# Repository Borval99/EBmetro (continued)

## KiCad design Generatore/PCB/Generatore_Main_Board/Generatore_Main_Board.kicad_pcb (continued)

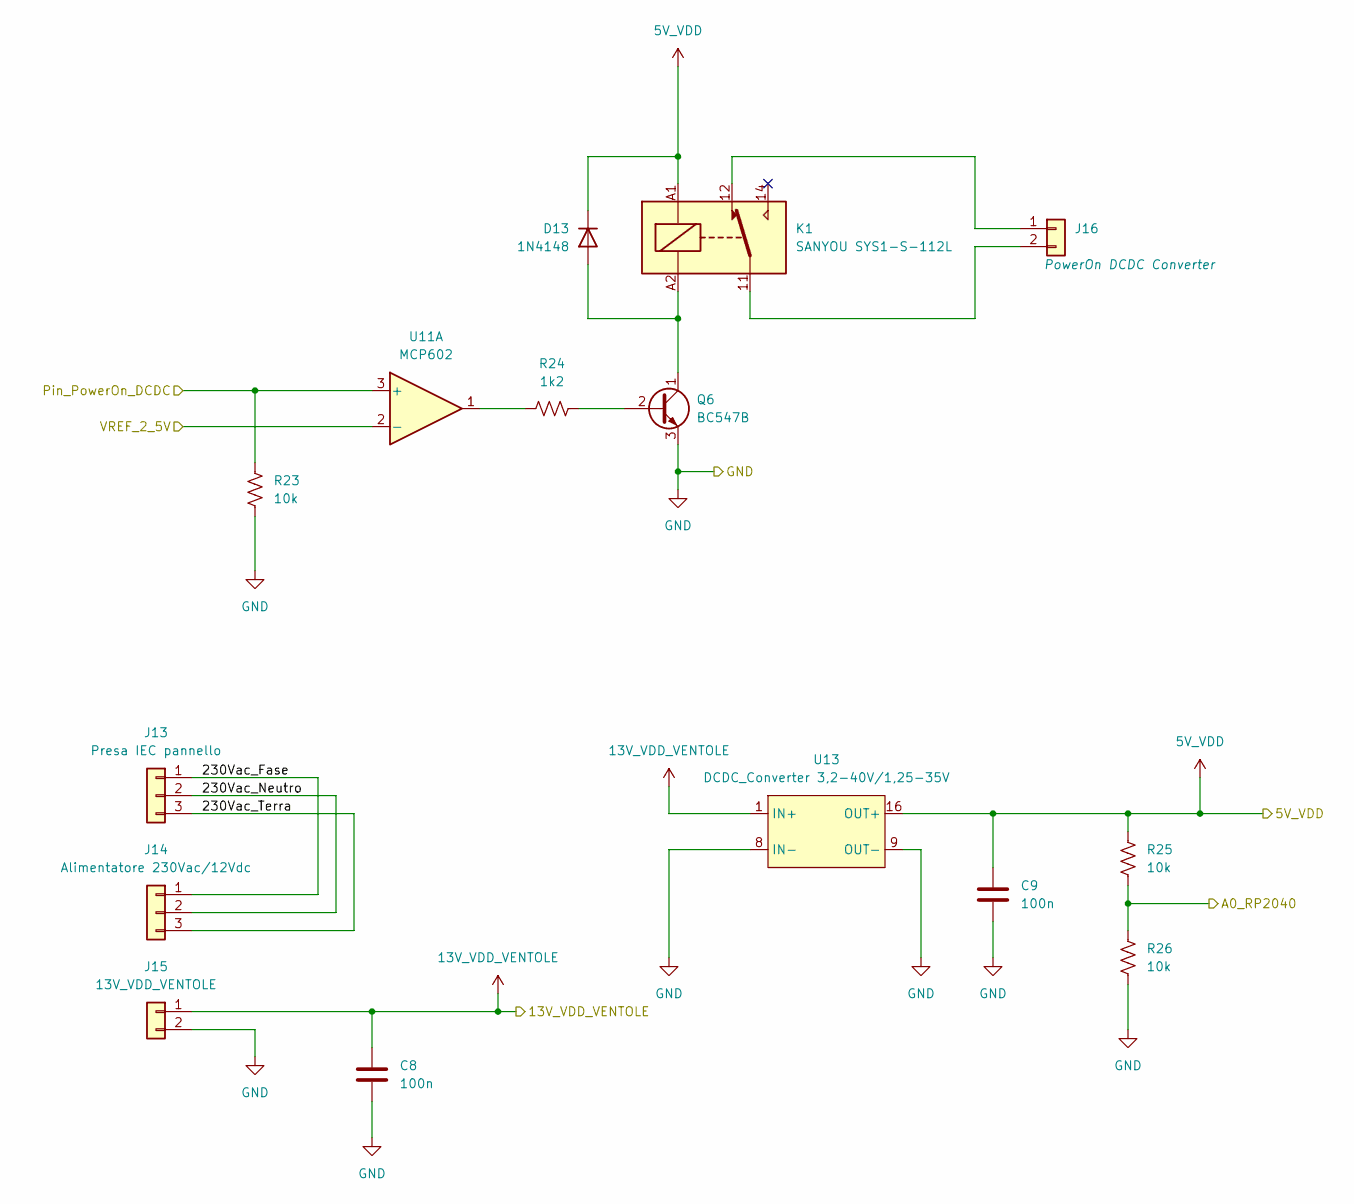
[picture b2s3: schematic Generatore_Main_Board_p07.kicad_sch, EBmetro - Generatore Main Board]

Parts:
C8, C9: 100n; Term_Block_1x2_P5mm
D13: 1N4148; D_DO-35_SOD27_P7.62mm_Horizontal
J13: Presa IEC pannello; TerminalBlock_Phoenix_MKDS-3-3-5.08_1x03_P5.08mm_Horizontal
J14: Alimentatore 230Vac/12Vdc; TerminalBlock_Phoenix_MKDS-3-3-5.08_1x03_P5.08mm_Horizontal
J15: 13V_VDD_VENTOLE; TerminalBlock_Phoenix_MKDS-3-2-5.08_1x02_P5.08mm_Horizontal
J16: Conn_01x02; JST_EH_B2B-EH-A_1x02_P2.50mm_Vertical
K1: SANYOU SYS1-S-112L; Relay_SPDT_Sanyou_SYS1-S-112L
Q6: BC547B; TO-92_Inline
R23, R25, R26: 10k; R_Axial_DIN0207_L6.3mm_D2.5mm_P10.16mm_Horizontal
R24: 1k2; R_Axial_DIN0207_L6.3mm_D2.5mm_P10.16mm_Horizontal
U11: MCP602; CERDIP-8_W7.62mm_SideBrazed_LongPads_Socket
U13: DCDC_Converter 3,2-40V/1,25-35V; DCDC_Converter 3,2-40V_1,25-35V

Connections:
5V_VDD: C9.1, D13.1 (K), K1.A1, R25.1, U13.16 (OUT+); also elsewhere on the board
13V_VDD_VENTOLE: C8.1, J15.1, U13.1 (IN+); also elsewhere on the board
/ADCs and Signal Conversion/VREF_2_5V: U11.2 (-); also elsewhere on the board
/CPUs/A0_RP2040: R25.2, R26.1; also elsewhere on the board
/CPUs/Pin_PowerOn_DCDC: R23.1, U11.3 (+); also elsewhere on the board
/Power and related/230Vac_Fase: J13.1, J14.1
/Power and related/230Vac_Neutro: J13.2, J14.2
/Power and related/230Vac_Terra: J13.3, J14.3
GND: C8.2, C9.2, J15.2, Q6.3 (E), R23.2, R26.2, U13.8 (IN-), U13.9 (OUT-); also elsewhere on the board
unnamed: D13.2 (A), K1.A2, Q6.1 (C)
unnamed: J16.1, K1.12
unnamed: J16.2, K1.11
unnamed: Q6.2 (B), R24.2
unnamed: R24.1, U11.1

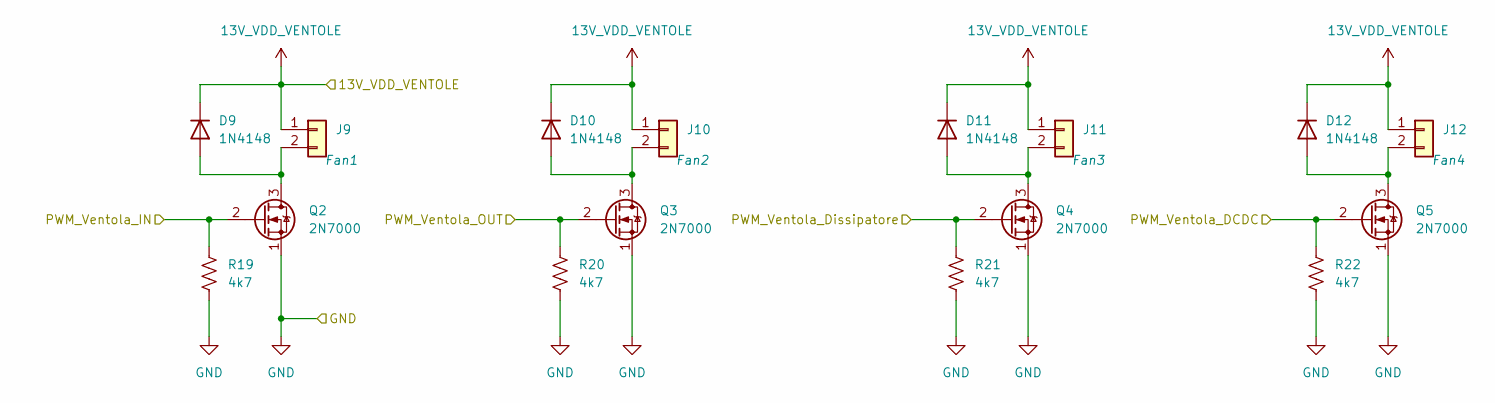
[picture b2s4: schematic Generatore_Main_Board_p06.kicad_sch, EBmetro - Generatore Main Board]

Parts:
D9, D10, D11, D12: 1N4148; D_DO-35_SOD27_P7.62mm_Horizontal
J9, J10, J11, J12: Conn_01x02; JST_XH_B2B-XH-A_1x02_P2.50mm_Vertical
Q2, Q3, Q4, Q5: 2N7000; TO-92_Inline
R19, R20, R21, R22: 4k7; R_Axial_DIN0207_L6.3mm_D2.5mm_P10.16mm_Horizontal

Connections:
13V_VDD_VENTOLE: D9.1 (K), D10.1 (K), D11.1 (K), D12.1 (K), J9.1, J10.1, J11.1, J12.1; also elsewhere on the board
/CPUs/PWM_Ventola_DCDC: Q5.2 (G), R22.1; also elsewhere on the board
/CPUs/PWM_Ventola_Dissipatore: Q4.2 (G), R21.1; also elsewhere on the board
/CPUs/PWM_Ventola_IN: Q2.2 (G), R19.1; also elsewhere on the board
/CPUs/PWM_Ventola_OUT: Q3.2 (G), R20.1; also elsewhere on the board
GND: Q2.1 (S), Q3.1 (S), Q4.1 (S), Q5.1 (S), R19.2, R20.2, R21.2, R22.2; also elsewhere on the board
unnamed: D9.2 (A), J9.2, Q2.3 (D)
unnamed: D10.2 (A), J10.2, Q3.3 (D)
unnamed: D11.2 (A), J11.2, Q4.3 (D)
unnamed: D12.2 (A), J12.2, Q5.3 (D)

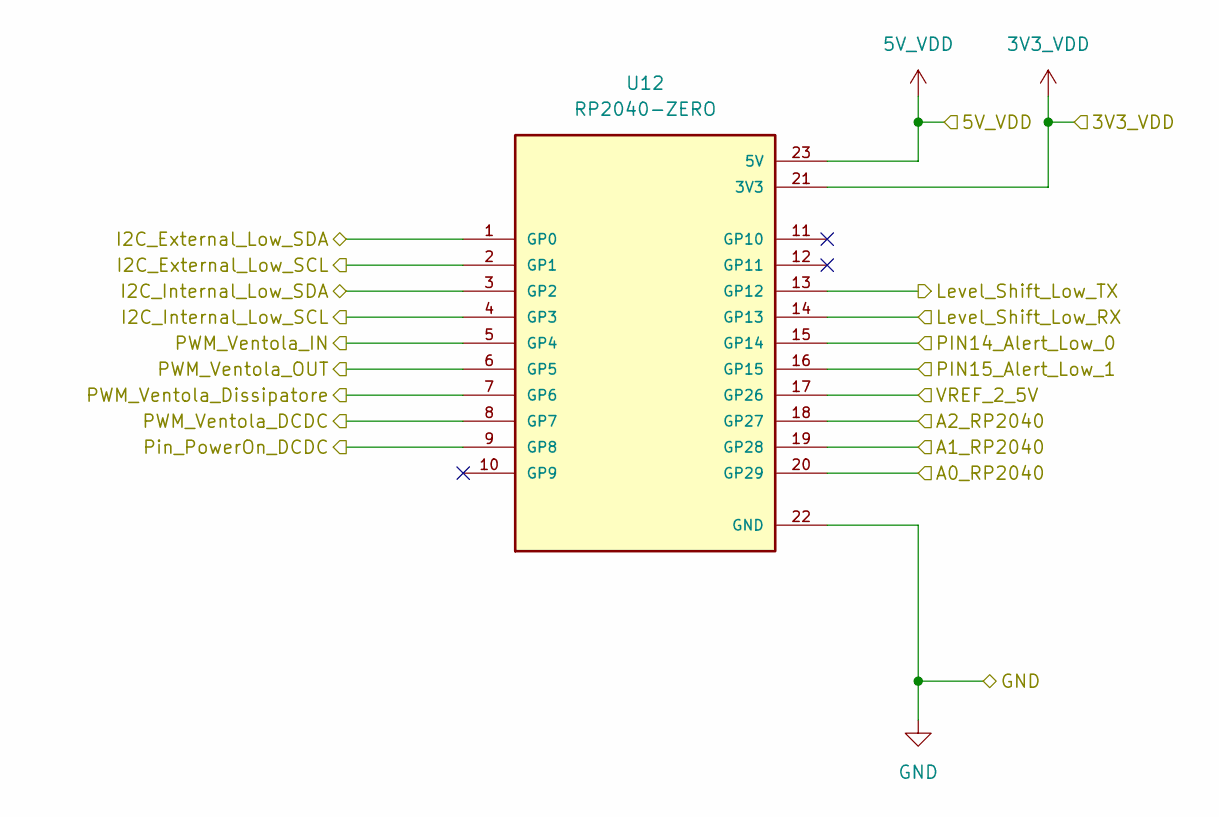
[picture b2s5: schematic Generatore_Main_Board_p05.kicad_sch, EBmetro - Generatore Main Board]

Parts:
U12: RP2040-ZERO; MODULE_RP2040-ZERO; PARTREV NA

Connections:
3V3_VDD: U12.21 (3V3); also elsewhere on the board
5V_VDD: U12.23 (5V); also elsewhere on the board
/ADCs and Signal Conversion/I2C_External_Low_SCL: U12.2 (GP1); also elsewhere on the board
/ADCs and Signal Conversion/I2C_External_Low_SDA: U12.1 (GP0); also elsewhere on the board
/ADCs and Signal Conversion/I2C_Internal_Low_SCL: U12.4 (GP3); also elsewhere on the board
/ADCs and Signal Conversion/I2C_Internal_Low_SDA: U12.3 (GP2); also elsewhere on the board
/ADCs and Signal Conversion/Level_Shift_Low_RX: U12.14 (GP13); also elsewhere on the board
/ADCs and Signal Conversion/Level_Shift_Low_TX: U12.13 (GP12); also elsewhere on the board
/ADCs and Signal Conversion/PIN14_Alert_Low_0: U12.15 (GP14); also elsewhere on the board
/ADCs and Signal Conversion/PIN15_Alert_Low_1: U12.16 (GP15); also elsewhere on the board
/ADCs and Signal Conversion/VREF_2_5V: U12.17 (GP26); also elsewhere on the board
/CPUs/A0_RP2040: U12.20 (GP29); also elsewhere on the board
/CPUs/A1_RP2040: U12.19 (GP28); also elsewhere on the board
/CPUs/A2_RP2040: U12.18 (GP27); also elsewhere on the board
/CPUs/PWM_Ventola_DCDC: U12.8 (GP7); also elsewhere on the board
/CPUs/PWM_Ventola_Dissipatore: U12.7 (GP6); also elsewhere on the board
/CPUs/PWM_Ventola_IN: U12.5 (GP4); also elsewhere on the board
/CPUs/PWM_Ventola_OUT: U12.6 (GP5); also elsewhere on the board
/CPUs/Pin_PowerOn_DCDC: U12.9 (GP8); also elsewhere on the board
GND: U12.22 (GND); also elsewhere on the board

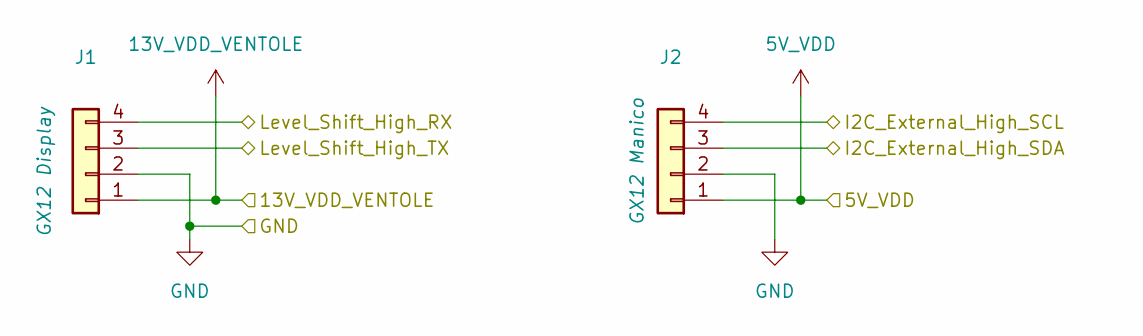
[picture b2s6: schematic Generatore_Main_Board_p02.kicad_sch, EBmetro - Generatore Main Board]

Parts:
J1, J2: Conn_01x04; JST_XH_B4B-XH-A_1x04_P2.50mm_Vertical

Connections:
5V_VDD: J2.1; also elsewhere on the board
13V_VDD_VENTOLE: J1.1; also elsewhere on the board
/ADCs and Signal Conversion/I2C_External_High_SCL: J2.4; also elsewhere on the board
/ADCs and Signal Conversion/I2C_External_High_SDA: J2.3; also elsewhere on the board
/ADCs and Signal Conversion/Level_Shift_High_RX: J1.4; also elsewhere on the board
/ADCs and Signal Conversion/Level_Shift_High_TX: J1.3; also elsewhere on the board
GND: J1.2, J2.2; also elsewhere on the board

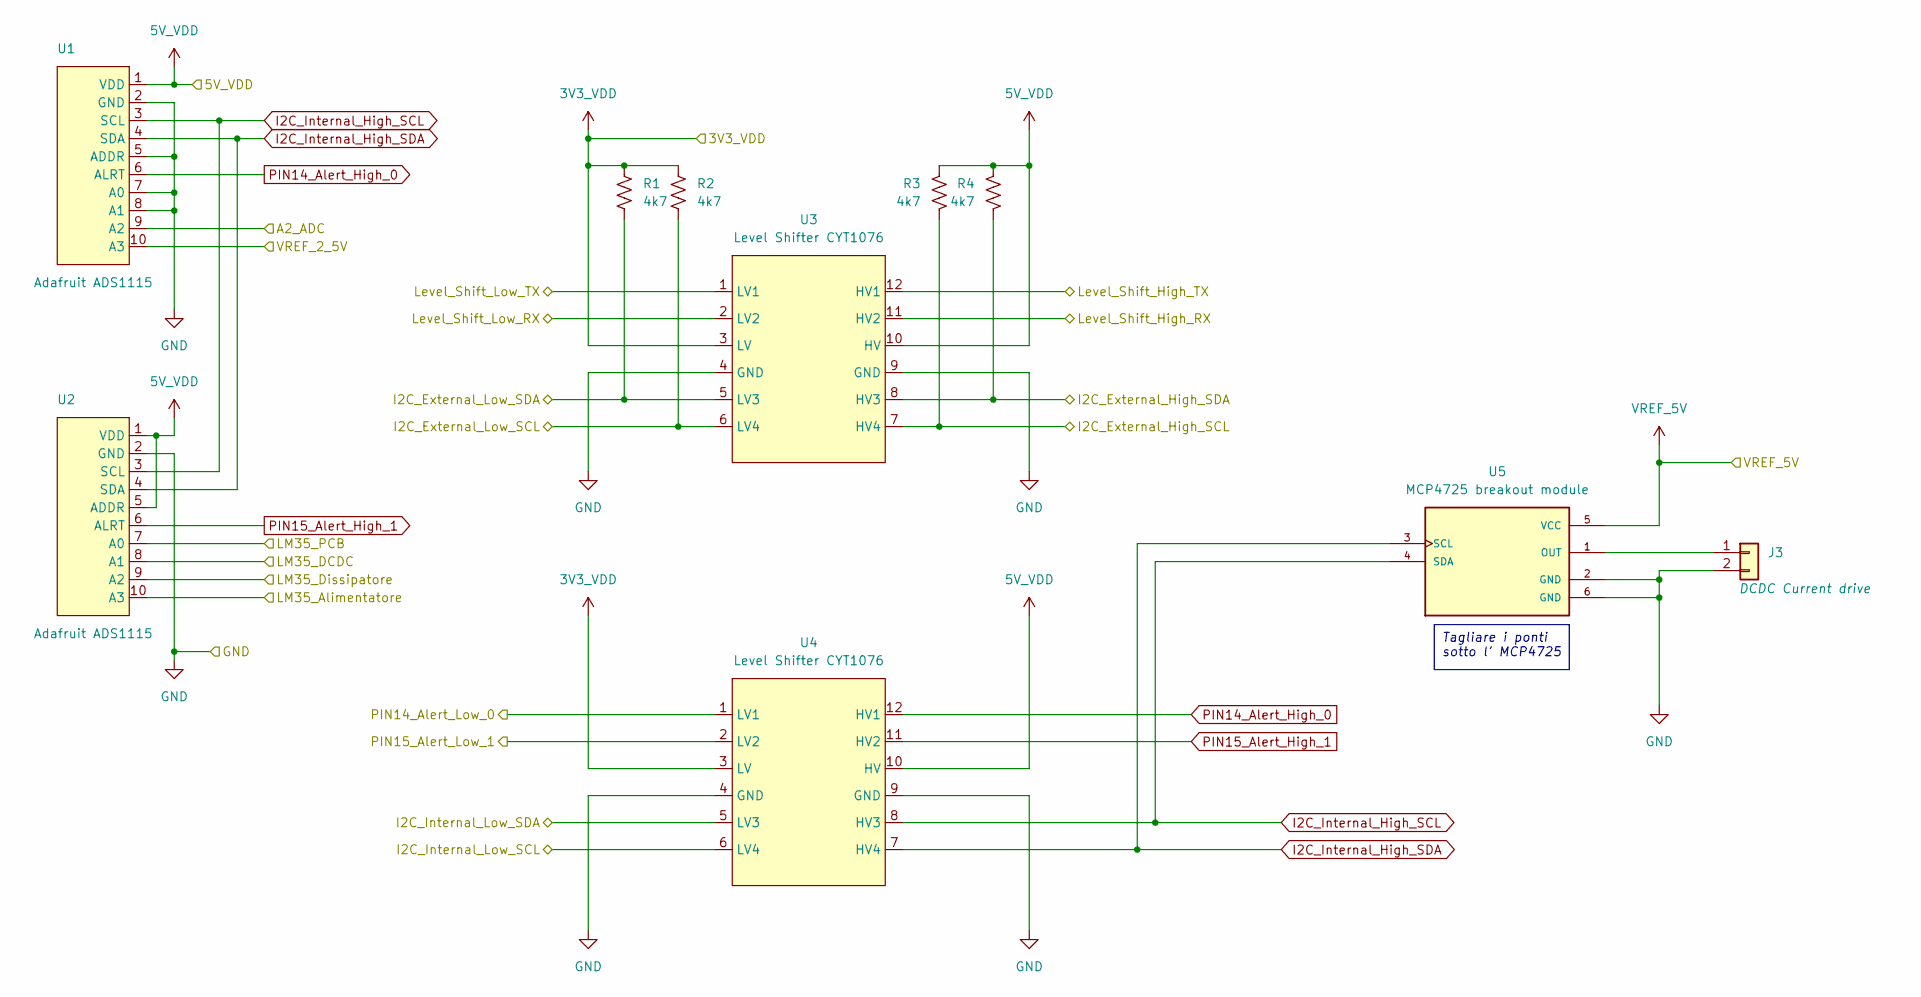
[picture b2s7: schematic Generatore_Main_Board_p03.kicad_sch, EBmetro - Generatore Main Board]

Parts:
J3: Conn_01x02; JST_EH_B2B-EH-A_1x02_P2.50mm_Vertical
R1, R2, R3, R4: 4k7; R_Axial_DIN0207_L6.3mm_D2.5mm_P10.16mm_Horizontal
U1, U2: Adafruit ADS1115; PinSocket_1x10_P2.54mm_Vertical
U3, U4: Level Shifter CYT1076; LevelShifter_CYT1076
U5: MCP4725 breakout module; MODULE_ZC576300; PARTREV v14

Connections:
3V3_VDD: R1.1, R2.1, U3.3 (LV), U4.3 (LV); also elsewhere on the board
5V_VDD: R3.1, R4.1, U1.1 (VDD), U2.1 (VDD), U2.5 (ADDR), U3.10 (HV), U4.10 (HV); also elsewhere on the board
/ADCs and Signal Conversion/A2_ADC: U1.9 (A2); also elsewhere on the board
/ADCs and Signal Conversion/I2C_External_High_SCL: R3.2, U3.7 (HV4); also elsewhere on the board
/ADCs and Signal Conversion/I2C_External_High_SDA: R4.2, U3.8 (HV3); also elsewhere on the board
/ADCs and Signal Conversion/I2C_External_Low_SCL: R2.2, U3.6 (LV4); also elsewhere on the board
/ADCs and Signal Conversion/I2C_External_Low_SDA: R1.2, U3.5 (LV3); also elsewhere on the board
/ADCs and Signal Conversion/I2C_Internal_Low_SCL: U4.6 (LV4); also elsewhere on the board
/ADCs and Signal Conversion/I2C_Internal_Low_SDA: U4.5 (LV3); also elsewhere on the board
/ADCs and Signal Conversion/LM35_Alimentatore: U2.10 (A3); also elsewhere on the board
/ADCs and Signal Conversion/LM35_DCDC: U2.8 (A1); also elsewhere on the board
/ADCs and Signal Conversion/LM35_Dissipatore: U2.9 (A2); also elsewhere on the board
/ADCs and Signal Conversion/LM35_PCB: U2.7 (A0); also elsewhere on the board
/ADCs and Signal Conversion/Level_Shift_High_RX: U3.11 (HV2); also elsewhere on the board
/ADCs and Signal Conversion/Level_Shift_High_TX: U3.12 (HV1); also elsewhere on the board
/ADCs and Signal Conversion/Level_Shift_Low_RX: U3.2 (LV2); also elsewhere on the board
/ADCs and Signal Conversion/Level_Shift_Low_TX: U3.1 (LV1); also elsewhere on the board
/ADCs and Signal Conversion/PIN14_Alert_Low_0: U4.1 (LV1); also elsewhere on the board
/ADCs and Signal Conversion/PIN15_Alert_Low_1: U4.2 (LV2); also elsewhere on the board
/ADCs and Signal Conversion/VREF_2_5V: U1.10 (A3); also elsewhere on the board
GND: J3.2, U1.2 (GND), U1.5 (ADDR), U1.7 (A0), U1.8 (A1), U2.2 (GND), U3.4 (GND), U3.9 (GND), U4.4 (GND), U4.9 (GND), U5.2 (GND), U5.6 (GND); also elsewhere on the board
I2C_Internal_High_SCL: U1.3 (SCL), U2.3 (SCL), U4.8 (HV3), U5.4 (SDA)
I2C_Internal_High_SDA: U1.4 (SDA), U2.4 (SDA), U4.7 (HV4), U5.3 (SCL)
unnamed: J3.1, U5.1 (OUT)
PIN14_Alert_High_0: U1.6 (ALRT), U4.12 (HV1)
PIN15_Alert_High_1: U2.6 (ALRT), U4.11 (HV2)
VREF_5V: U5.5 (VCC); also elsewhere on the board

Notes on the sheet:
Tagliare i ponti sotto l' MCP4725

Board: 2 copper layers, 86 parts (0 on the bottom side), 68 nets, no tracks yet.

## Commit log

2026-04-02 Massive Update
